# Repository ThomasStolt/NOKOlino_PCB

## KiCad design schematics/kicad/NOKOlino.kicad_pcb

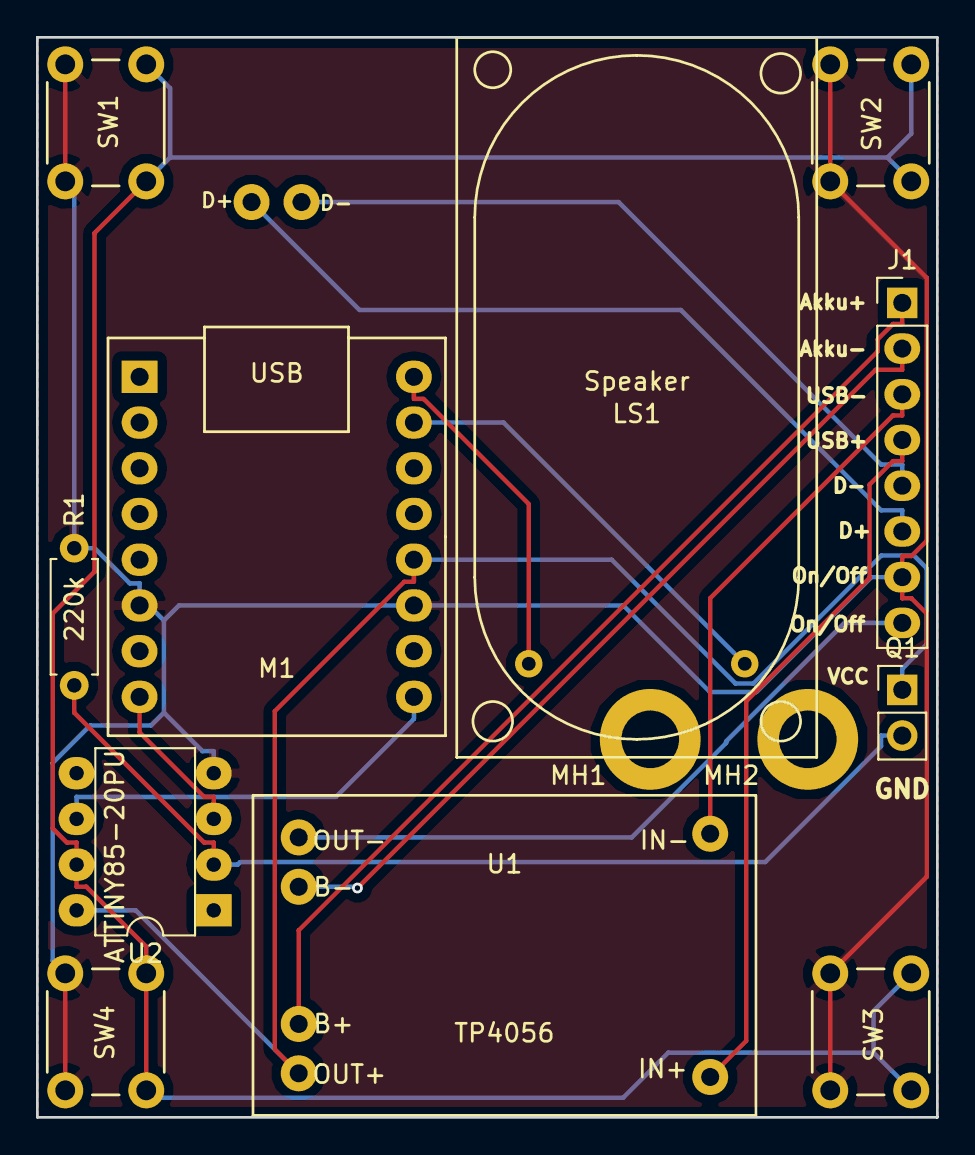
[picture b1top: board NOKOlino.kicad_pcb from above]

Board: 2 copper layers, 50.0 x 60.0 mm, 13 parts (0 on the bottom side), 15 nets.

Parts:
J1: CONN_01X08; Pin_Header_Straight_1x08_Pitch2.54mm
LS1: Speaker; K20.40
M1: JQ6500; JQ6500-16p
MH1: MH1; MountingHole_3.2mm_M3_DIN965_Pad
MH2: MH2; MountingHole_3.2mm_M3_DIN965_Pad
Q1: Q_Photo_NPN; Pin_Header_Straight_1x02_Pitch2.54mm
R1: 220k; R_Axial_DIN0207_L6.3mm_D2.5mm_P7.62mm_Horizontal
SW1: SW1; SW_PUSH_6mm_h13mm
SW2: SW2; SW_PUSH_6mm_h13mm
SW3: SW3; SW_PUSH_6mm_h13mm
SW4: SW4; SW_PUSH_6mm_h13mm
U1: TP4056; TP4056-Protect
U2: ATTINY85-20PU

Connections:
Akku+: J1.1, U1.4
Akku-: J1.2, U1.5
D+: J1.6, M1.18
D-: J1.5, M1.17
GND: J1.7, M1.6, M1.11, R1.2, SW1.1, SW2.1, SW3.1, SW4.1, U2.4
unnamed: LS1.1, M1.16
unnamed: LS1.2, M1.15
unnamed: M1.8, U2.3
unnamed: M1.9, U2.6
unnamed: Q1.2, R1.1, U2.2
unnamed: SW1.2, SW2.2, SW3.2, SW4.2, U2.7
SW5: J1.8, U1.6
USB+: J1.4, U1.1
USB-: J1.3, U1.2
VCC: M1.12, Q1.1, U1.3, U2.8

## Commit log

2018-09-04 Changes to the PCB, added foto transistor
2018-09-05 changed top PCB
